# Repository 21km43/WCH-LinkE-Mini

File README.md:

# WCH-LinkE-Mini

This project is compatible with WCH-LinkE.

Boards is optimized for [JLCPCB](https://jlcpcb.com) (includes gerber, bom, cpl, and tooling holes). All components except the CH32V305, USB-C Connector, and 3.3V LDO are Basic Parts.

## Requirements
* [KiCAD 9.0](https://www.kicad.org/)
* [Fabrication-Toolkit (Optional)](https://github.com/bennymeg/Fabrication-Toolkit)

## LICENSE
[MIT LICENSE](/LICENSE)

## Production files
- [Gerber](/production/WCH-LinkE-Mini_v1.4.0.zip)
- [BOM](/production/bom.csv)

## Schematic and Board image
[Board schematic](WCH-LinkE-Mini.pdf)  

IDC Connectors are available here
- [IDC-Header(socket)](https://www.digikey.jp/ja/products/detail/sullins-connector-solutions/SBH11-PBPC-D05-ST-BK/1990062)
- [IDC-Header(header)](https://www.digikey.jp/ja/products/detail/sullins-connector-solutions/SFH11-PBPC-D05-ST-BK/1990087)

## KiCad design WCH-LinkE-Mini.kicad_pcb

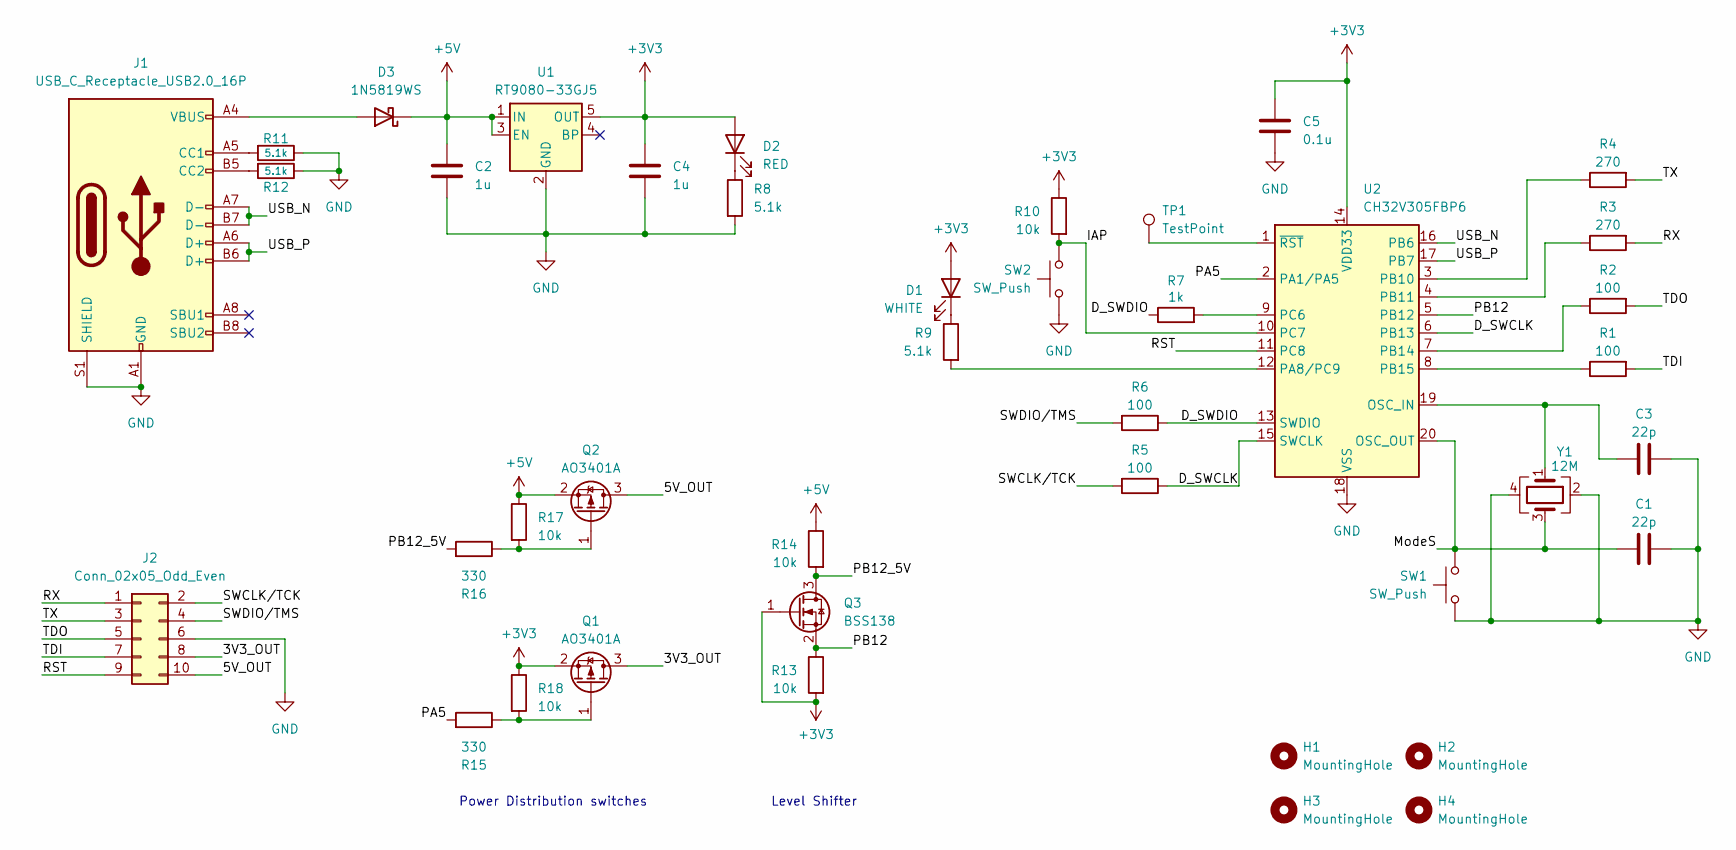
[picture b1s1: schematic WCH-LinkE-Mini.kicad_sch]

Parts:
C1, C3: 22p; C_0402_1005Metric; LCSC Part # C1555
C2, C4: 1u; C_0402_1005Metric; LCSC Part # C52923
C5: 0.1u; C_0402_1005Metric; LCSC Part # C1525
D1: WHITE; LED_0603_1608Metric; LCSC Part # C2290
D2: RED; LED_0603_1608Metric; LCSC Part # C2286
D3: 1N5819WS; D_SOD-323; LCSC Part # C191023
H1, H2, H3, H4: MountingHole; Tooling_Hole
J1: USB_C_Receptacle_USB2.0_16P; USB_C_Receptacle; LCSC Part # C2988369
J2: Conn_02x05_Odd_Even; PinHeader_2x05_P2.54mm_Horizontal_SMD
Q1, Q2: AO3401A; SOT-23; LCSC Part # C15127
Q3: BSS138; SOT-23; LCSC Part # C7420339
R1, R2, R5, R6: 100; R_0402_1005Metric; LCSC Part # C25076
R3, R4: 270; R_0603_1608Metric; LCSC Part # C22966
R7: 1k; R_0402_1005Metric; LCSC Part # C11702
R8, R9, R11, R12: 5.1k; R_0402_1005Metric; LCSC Part # C25905
R10, R13, R14, R17, R18: 10k; R_0402_1005Metric; LCSC Part # C25744
R15, R16: 330; R_0402_1005Metric; LCSC Part # C25104
SW1, SW2: SW_Push; TS-1088-AR02016; LCSC Part # C720477
TP1: TestPoint; TestPoint_Pad_D1.5mm
U1: RT9080-33GJ5; SOT-23-5; LCSC Part # C841192
U2: CH32V305FBP6; TSSOP-20_4.4x6.5mm_P0.65mm; LCSC Part # C5123443
Y1: 12M; Crystal_SMD_3225-4Pin_3.2x2.5mm; LCSC Part # C9002

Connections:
+3V3: C4.1, C5.1, D1.2 (A), D2.2 (A), Q1.2 (S), Q3.1 (G), R10.1, R13.2, R18.1, U1.5 (OUT), U2.14 (VDD33)
+5V: C2.1, D3.1 (K), Q2.2 (S), R14.1, R17.1, U1.1 (IN), U1.3 (EN)
/3V3_OUT: J2.8, Q1.3 (D)
/5V_OUT: J2.10, Q2.3 (D)
/D_SWCLK: R5.1, U2.6 (PB13), U2.15 (SWCLK)
/D_SWDIO: R6.1, R7.1, U2.13 (SWDIO)
/IAP: R10.2, SW2.1, U2.10 (PC7)
/ModeS: C1.2, SW1.1, U2.20 (OSC_OUT), Y1.3
/PA5: R15.2, U2.2 (PA1/PA5)
/PB12: Q3.2 (S), R13.1, U2.5 (PB12)
/PB12_5V: Q3.3 (D), R14.2, R16.2
/RST: J2.9, U2.11 (PC8)
/RX: J2.1, R3.2
/SWCLK/TCK: J2.2, R5.2
/SWDIO/TMS: J2.4, R6.2
/TDI: J2.7, R1.2
/TDO: J2.5, R2.2
/TX: J2.3, R4.2
/USB_N: J1.A7 (D-), J1.B7 (D-), U2.16 (PB6)
/USB_P: J1.A6 (D+), J1.B6 (D+), U2.17 (PB7)
GND: C1.1, C2.2, C3.1, C4.2, C5.2, J1.A1 (GND), J1.A12 (GND), J1.B1 (GND), J1.B12 (GND), J1.S1 (SHIELD), J2.6, R8.2, R11.1, R12.1, SW1.2, SW2.2, U1.2 (GND), U2.18 (VSS), Y1.2, Y1.4
unnamed: D1.1 (K), R9.1
unnamed: D2.1 (K), R8.1
unnamed: D3.2 (A), J1.A4 (VBUS), J1.A9 (VBUS), J1.B4 (VBUS), J1.B9 (VBUS)
unnamed: J1.A5 (CC1), R11.2
unnamed: J1.B5 (CC2), R12.2
unnamed: Q1.1 (G), R15.1, R18.2
unnamed: Q2.1 (G), R16.1, R17.2
unnamed: C3.2, U2.19 (OSC_IN), Y1.1
unnamed: R9.2, U2.12 (PA8/PC9)
unnamed: R4.1, U2.3 (PB10)
unnamed: R3.1, U2.4 (PB11)
unnamed: R2.1, U2.7 (PB14)
unnamed: R1.1, U2.8 (PB15)
unnamed: R7.2, U2.9 (PC6)
unnamed: TP1.1, U2.1 (~RST)

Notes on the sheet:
Power Distribution switches
Level Shifter

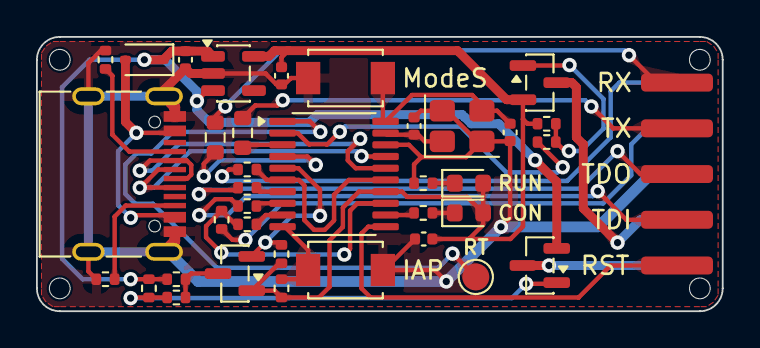
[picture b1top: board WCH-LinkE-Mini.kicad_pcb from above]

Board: 2 copper layers, 38.1 x 15.2 mm, 41 parts (0 on the bottom side), 36 nets.

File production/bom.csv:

Designator,Footprint,Quantity,Value,LCSC Part #
"C1, C3",0402,2,22p,C1555
"C2, C4",0402,2,1u,C52923
C5,0402,1,0.1u,C1525
D1,0603,1,WHITE,C2290
D2,0603,1,RED,C2286
D3,D_SOD-323,1,1N5819WS,C191023
J1,USB_C_Receptacle,1,USB_C_Receptacle_USB2.0_16P,C2988369
"Q1, Q2",SOT-23,2,AO3401A,C15127
Q3,SOT-23,1,BSS138,C7420339
"R1, R2, R5, R6",0402,4,100,C25076
"R10, R13, R14, R17, R18",0402,5,10k,C25744
"R11, R12, R8, R9",0402,4,5.1k,C25905
"R15, R16",0402,2,330,C25104
"R3, R4",0603,2,270,C22966
R7,0402,1,1k,C11702
"SW1, SW2",TS-1088-AR02016,2,SW_Push,C720477
U1,SOT-23-5,1,RT9080-33GJ5,C841192
U2,TSSOP-20_4.4x6.5mm_P0.65mm,1,CH32V305FBP6,C5123443
Y1,Crystal_SMD_3225-4Pin_3.2x2.5mm,1,12M,C9002

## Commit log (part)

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2024-09-17 csv position fix
2024-09-17 update picture
2024-09-25 move ch217k
2024-09-26 position fix
2024-09-26 version fix and show previous version
2024-09-26 fix trace width
2024-09-26 fix trace for gnd
2024-09-27 optimize
2024-09-28 fix button footprint
2024-10-02 remove solder pastefrom pinheader
2024-10-03 fix library and fillzone
2024-10-06 v1.1.0 pre-release
2024-10-06 fix resistor value
2024-10-06 rename project
2024-10-06 fix path
2024-10-06 fix silk
2024-10-06 push test
2024-10-06 fix position
2024-10-09 change load switch structure
2024-10-09 v1.1.0
    position fix
    version fix and show previous version
    fix trace width
    fix trace for gnd
    Update README.md
    Update README.md
2024-10-09 fix readme
2024-10-10 add idc connector explain
2024-10-10 add remarks
2024-10-10 add resettable fuse
2025-01-08 v1.3.0
2025-01-08 remove yml
2025-01-08 v1.3.0 (#3)
    * v1.3.0
    * Create review.yml
    * remove yml
2025-01-08 Update production files
2025-10-14 Revise README with JLCPCB optimization information
    Updated README to include JLCPCB optimization details.
2025-10-15 Update README with additional component information
    Added details about component specifications and clarified parts list.
2025-12-12 update symbols and footprints
2025-12-13 v1.4.0
2025-12-28 Revise README with production files and formatting
    Updated the README to include production files and improved formatting.
2025-12-28 Revise README with additional component information
    Updated project details and added missing components.
